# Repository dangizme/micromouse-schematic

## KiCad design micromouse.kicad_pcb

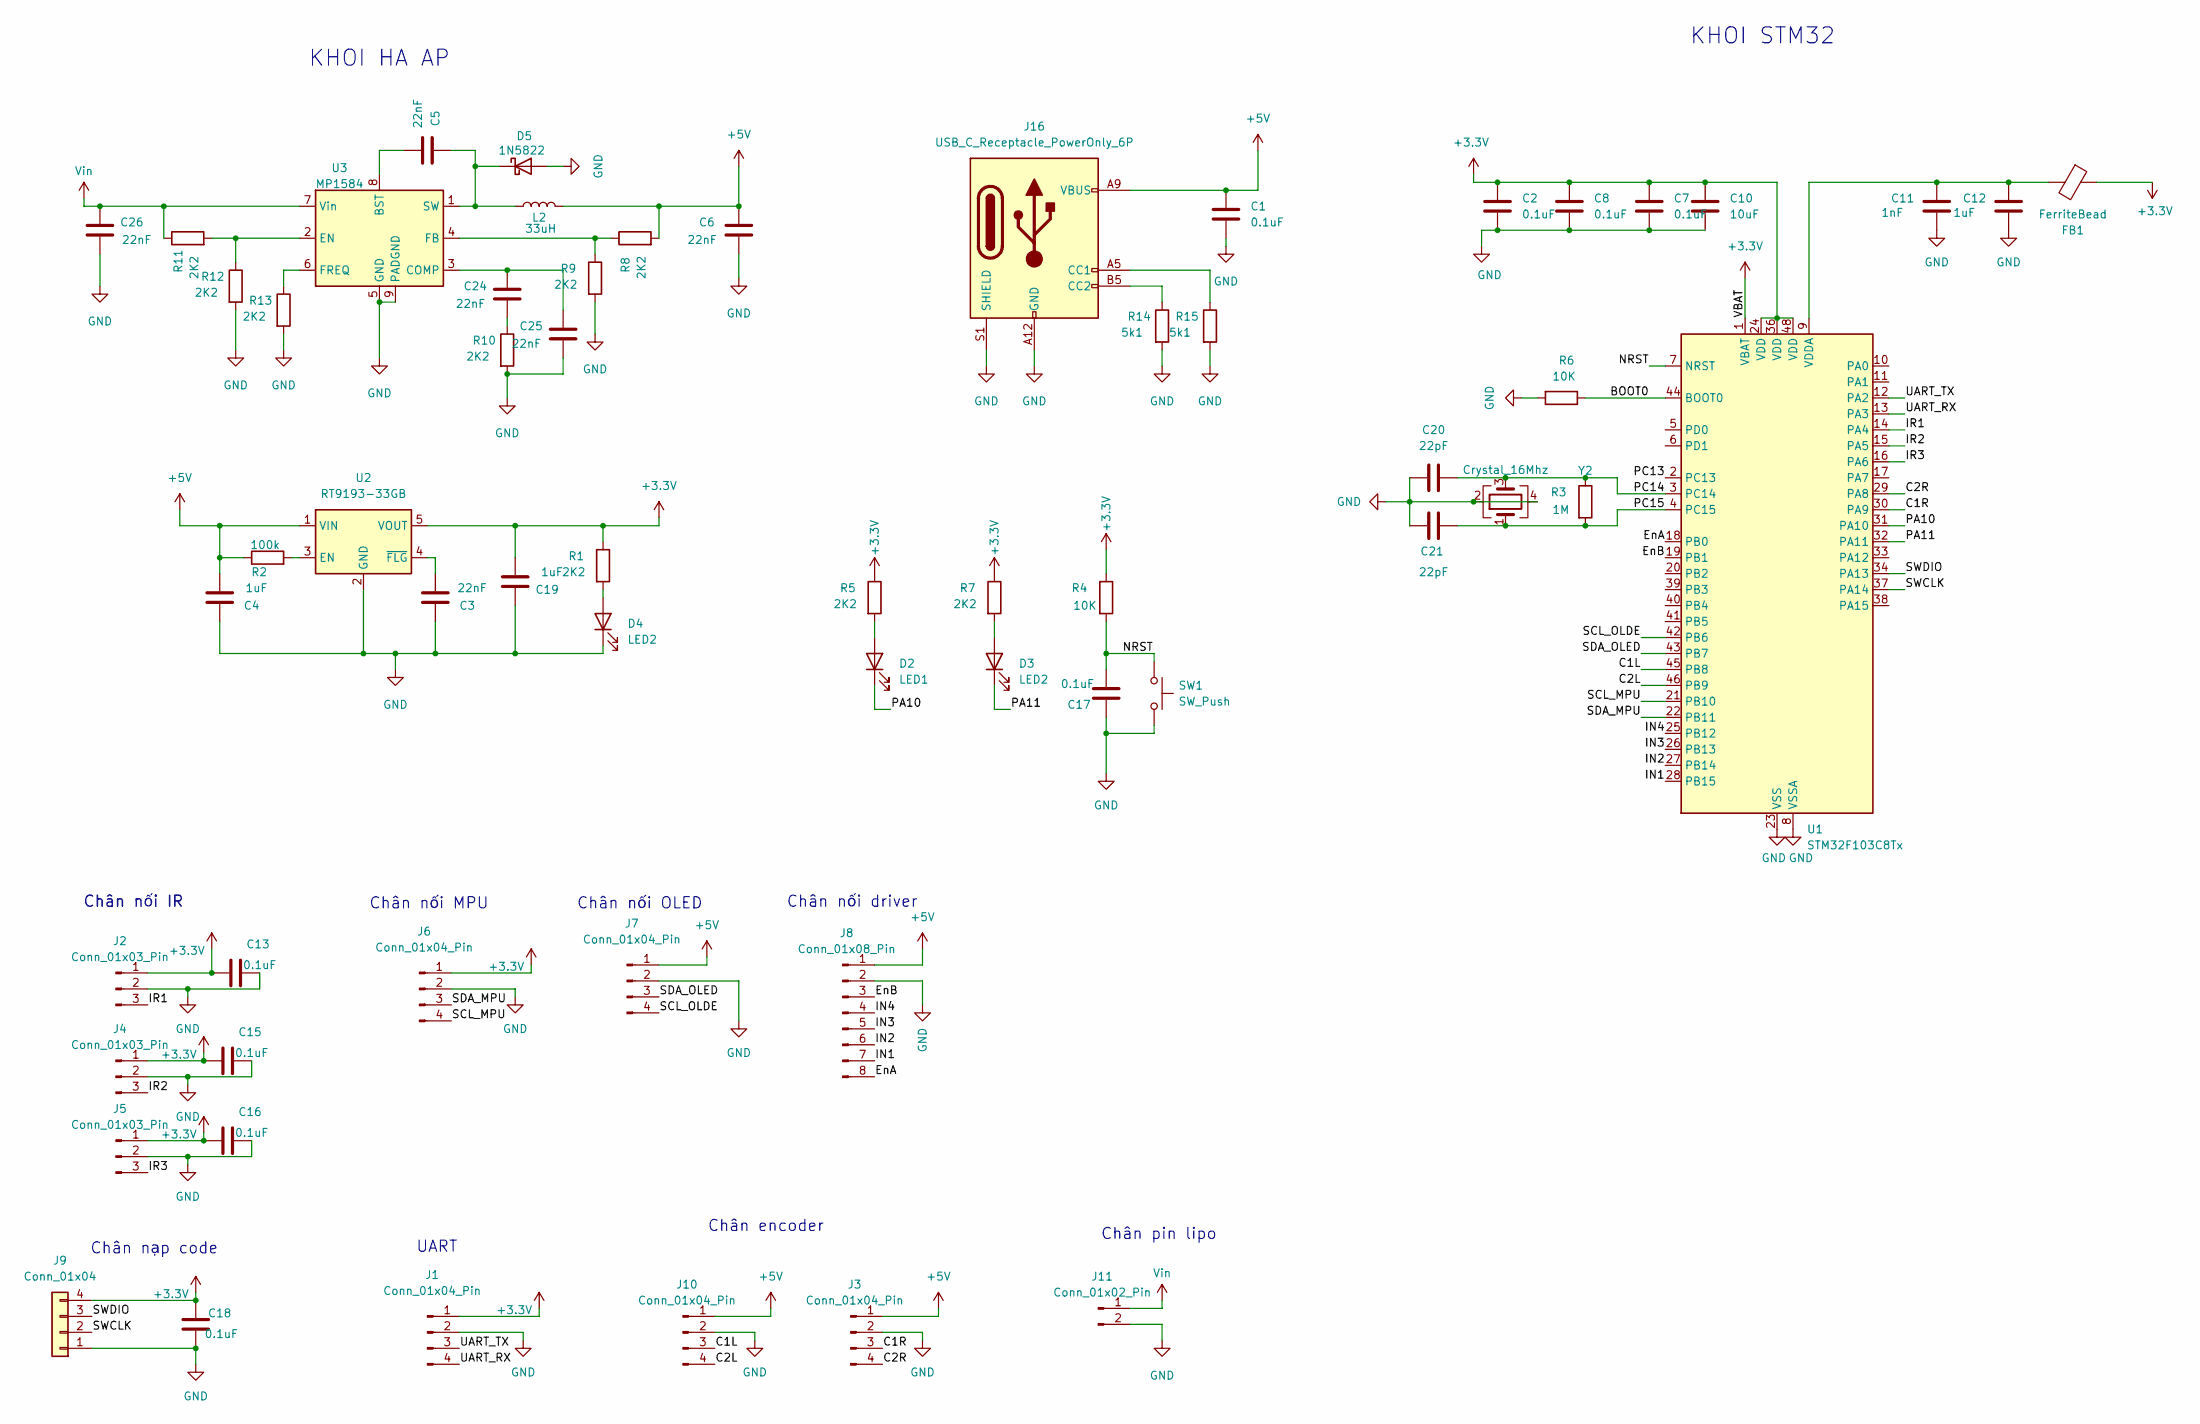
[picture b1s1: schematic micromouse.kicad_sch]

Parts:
C1, C2, C7, C8, C13, C15, C16, C17, C18: 0.1uF; C_0603_1608Metric
C3, C5, C6, C24, C25, C26: 22nF; C_0603_1608Metric
C4, C12, C19: 1uF; C_0603_1608Metric
C10: 10uF; C_1206_3216Metric
C11: 1nF; C_0603_1608Metric
C20, C21: 22pF; C_0603_1608Metric
D2: LED1; LED_0603_1608Metric_Pad1.05x0.95mm_HandSolder
D3, D4: LED2; LED_0603_1608Metric_Pad1.05x0.95mm_HandSolder
D5: 1N5822; D_SMA
FB1: FerriteBead; R_0603_1608Metric
J1, J3, J6, J7, J10: Conn_01x04_Pin; PinHeader_1x04_P2.54mm_Vertical
J2, J4, J5: Conn_01x03_Pin; PinHeader_1x03_P2.54mm_Vertical
J8: Conn_01x08_Pin; PinHeader_1x08_P2.54mm_Vertical
J9: Conn_01x04; PinHeader_1x04_P2.54mm_Vertical
J11: Conn_01x02_Pin; PinHeader_1x02_P2.54mm_Vertical
J16: USB_C_Receptacle_PowerOnly_6P; USB_C_Receptacle_GCT_USB4125-xx-x_6P_TopMnt_Horizontal; PART TYPE-C 6P
L2: 33uH; L_10.4x10.4_H4.8
R1, R5, R7, R8, R9, R10, R11, R12, R13: 2K2; R_0805_2012Metric_Pad1.20x1.40mm_HandSolder
R2: 100k; R_0805_2012Metric_Pad1.20x1.40mm_HandSolder
R3: 1M; R_0805_2012Metric_Pad1.20x1.40mm_HandSolder
R4, R6: 10K; R_0805_2012Metric_Pad1.20x1.40mm_HandSolder
R14, R15: 5k1; R_0805_2012Metric_Pad1.20x1.40mm_HandSolder
SW1: SW_Push; SW_Push_SPST_NO_Alps_SKRK
U1: STM32F103C8Tx; LQFP-48_7x7mm_P0.5mm
U2: RT9193-33GB; TSOT-23-5
U3: MP1584; SOIC-8-1EP_3.9x4.9mm_P1.27mm_EP2.29x3mm
Y2: Crystal_16Mhz; Crystal_SMD_2520-4Pin_2.5x2.0mm

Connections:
+3.3V: C2.2, C7.2, C8.2, C10.2, C13.2, C15.2, C16.2, C18.1, C19.2, FB1.1, J1.1, J2.1, J4.1, J5.1, J6.1, J9.4, R1.1, R4.1, R5.1, R7.1, U1.1 (VBAT), U1.24 (VDD), U1.36 (VDD), U1.48 (VDD), U2.5 (VOUT)
+5V: C1.2, C4.2, C6.1, J3.1, J7.1, J8.1, J10.1, J16.A9 (VBUS), J16.B9 (VBUS), L2.2, R2.1, R8.2, U2.1 (VIN)
/BOOT0: R6.1, U1.44 (BOOT0)
/C1L: J10.3, U1.45 (PB8)
/C1R: J3.3, U1.30 (PA9)
/C2L: J10.4, U1.46 (PB9)
/C2R: J3.4, U1.29 (PA8)
/EnA: J8.8, U1.18 (PB0)
/EnB: J8.3, U1.19 (PB1)
/IN1: J8.7, U1.28 (PB15)
/IN2: J8.6, U1.27 (PB14)
/IN3: J8.5, U1.26 (PB13)
/IN4: J8.4, U1.25 (PB12)
/IR1: J2.3, U1.14 (PA4)
/IR2: J4.3, U1.15 (PA5)
/IR3: J5.3, U1.16 (PA6)
/NRST: C17.2, R4.2, SW1.1, U1.7 (NRST)
/PA10: D2.1 (K), U1.31 (PA10)
/PA11: D3.1 (K), U1.32 (PA11)
/PC13: U1.2 (PC13)
/PC14: C20.2, R3.1, U1.3 (PC14), Y2.3
/PC15: C21.2, R3.2, U1.4 (PC15), Y2.1
/SCL_MPU: J6.4, U1.21 (PB10)
/SCL_OLDE: J7.4, U1.42 (PB6)
/SDA_MPU: J6.3, U1.22 (PB11)
/SDA_OLED: J7.3, U1.43 (PB7)
/SWCLK: J9.2, U1.37 (PA14)
/SWDIO: J9.3, U1.34 (PA13)
/UART_RX: J1.4, U1.13 (PA3)
/UART_TX: J1.3, U1.12 (PA2)
GND: C1.1, C2.1, C3.1, C4.1, C6.2, C7.1, C8.1, C10.1, C11.1, C12.1, C13.1, C15.1, C16.1, C17.1, C18.2, C19.1, C20.1, C21.1, C25.2, C26.2, D4.1 (K), D5.2 (A), J1.2, J2.2, J3.2, J4.2, J5.2, J6.2, J7.2, J8.2, J9.1, J10.2, J11.2, J16.A12 (GND), J16.B12 (GND), J16.S1 (SHIELD), R6.2, R9.2, R10.2, R12.2, R13.2, R14.2, R15.2, SW1.2, U1.8 (VSSA), U1.23 (VSS), U1.35 (VSS), U1.47 (VSS), U2.2 (GND), U3.5 (GND), U3.9 (PADGND), Y2.2, Y2.4
unnamed: C24.2, R10.1
unnamed: D2.2 (A), R5.2
unnamed: D3.2 (A), R7.2
unnamed: D4.2 (A), R1.2
unnamed: C5.1, D5.1 (K), L2.1, U3.1 (SW)
unnamed: J16.A5 (CC1), R15.1
unnamed: J16.B5 (CC2), R14.1
unnamed: C11.2, C12.2, FB1.2, U1.9 (VDDA)
unnamed: R2.2, U2.3 (EN)
unnamed: C3.2, U2.4 (~FLG)
unnamed: C5.2, U3.8 (BST)
unnamed: C24.1, C25.1, U3.3 (COMP)
unnamed: R11.2, R12.1, U3.2 (EN)
unnamed: R8.1, R9.1, U3.4 (FB)
unnamed: R13.1, U3.6 (FREQ)
Vin: C26.1, J11.1, R11.1, U3.7 (Vin)

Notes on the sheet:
Chân encoder
KHOI HA AP
Chân nối driver
Chân pin lipo
KHOI STM32
UART
Chân nối IR
Chân nối OLED
Chân nối MPU
Chân nạp code

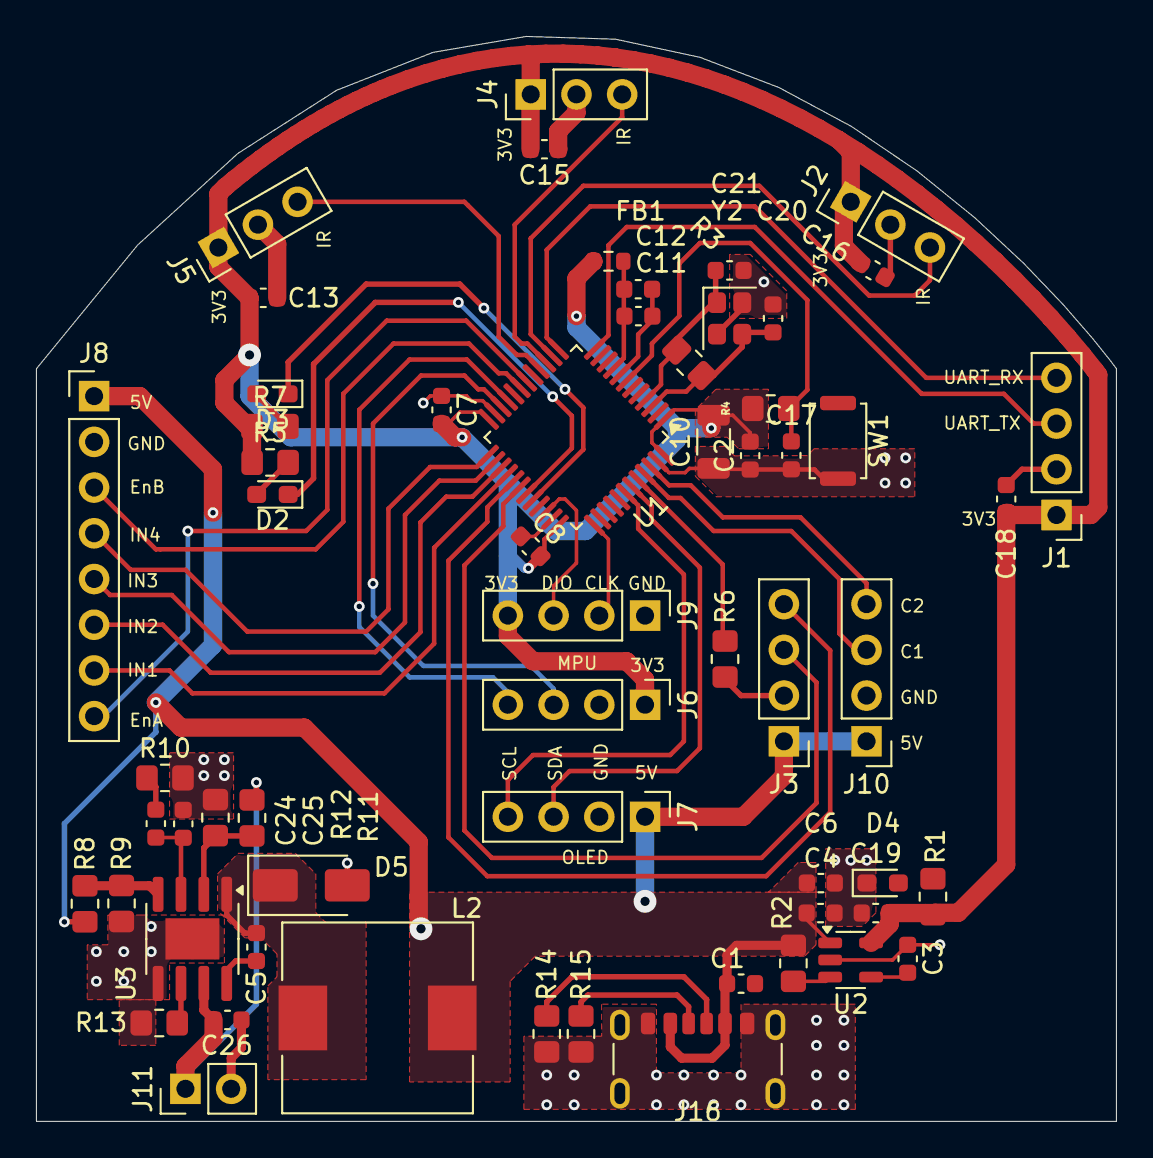
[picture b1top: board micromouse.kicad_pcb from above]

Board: 2 copper layers, 60.0 x 60.3 mm, 60 parts (0 on the bottom side), 46 nets.

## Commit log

2025-10-28 Day file KiCad len kho
2025-11-04 Cập nhật schematic
2025-11-23 cap nhat schematic
2025-12-21 cap nhat pcb
2026-01-06 LDH_ver1.0
